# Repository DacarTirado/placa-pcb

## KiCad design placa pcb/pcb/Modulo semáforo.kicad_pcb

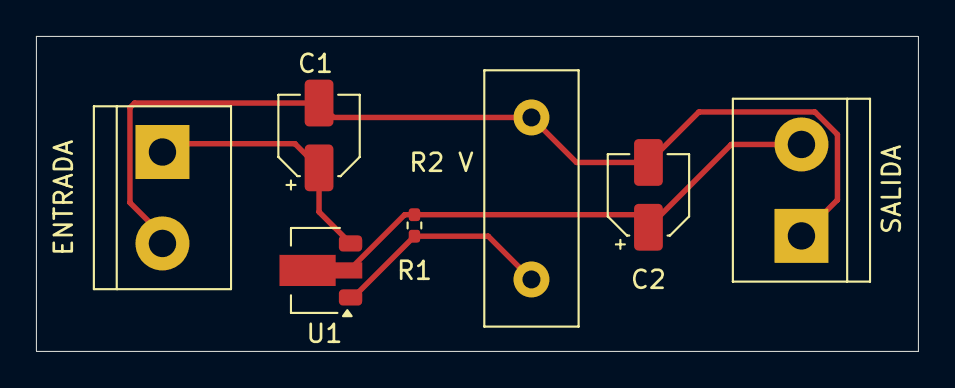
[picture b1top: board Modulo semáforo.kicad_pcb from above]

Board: 2 copper layers, 49.0 x 17.5 mm, 7 parts (0 on the bottom side), 4 nets.

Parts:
C1: 0.1uf; CP_Elec_4x3
C2: 47uf; CP_Elec_4x3
ENTRADA: TerminalBlock_bornier-2_P5.08mm
R1: 200; R_0402_1005Metric_Pad0.72x0.64mm_HandSolder
R2 V: 10K; R_Box_L14.0mm_W5.0mm_P9.00mm
SALIDA: TerminalBlock_bornier-2_P5.08mm
U1: LM317L_SOT-89; SOT-89-3

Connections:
GND: C1.2, C2.2, ENTRADA.2, R2 V.2, SALIDA.1
unnamed: R1.2, R2 V.1, U1.1 (ADJ)
VIN: C1.1, ENTRADA.1, U1.3 (VI)
VOUT: C2.1, R1.1, SALIDA.2, U1.2 (VO)
